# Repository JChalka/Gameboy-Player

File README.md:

# Gameboy Player
Custom Gameboy Player PCB
Currently not verified as working/functional
Use at your own risk

TODO:
Create better visuals for gamecube to GBP wiring directly to gamecube boards
Verify design
Fix signal integrity issues
Add FPGA to output a VGA/Component signal and bypass GBS-DOL chip, as well as pass through controls

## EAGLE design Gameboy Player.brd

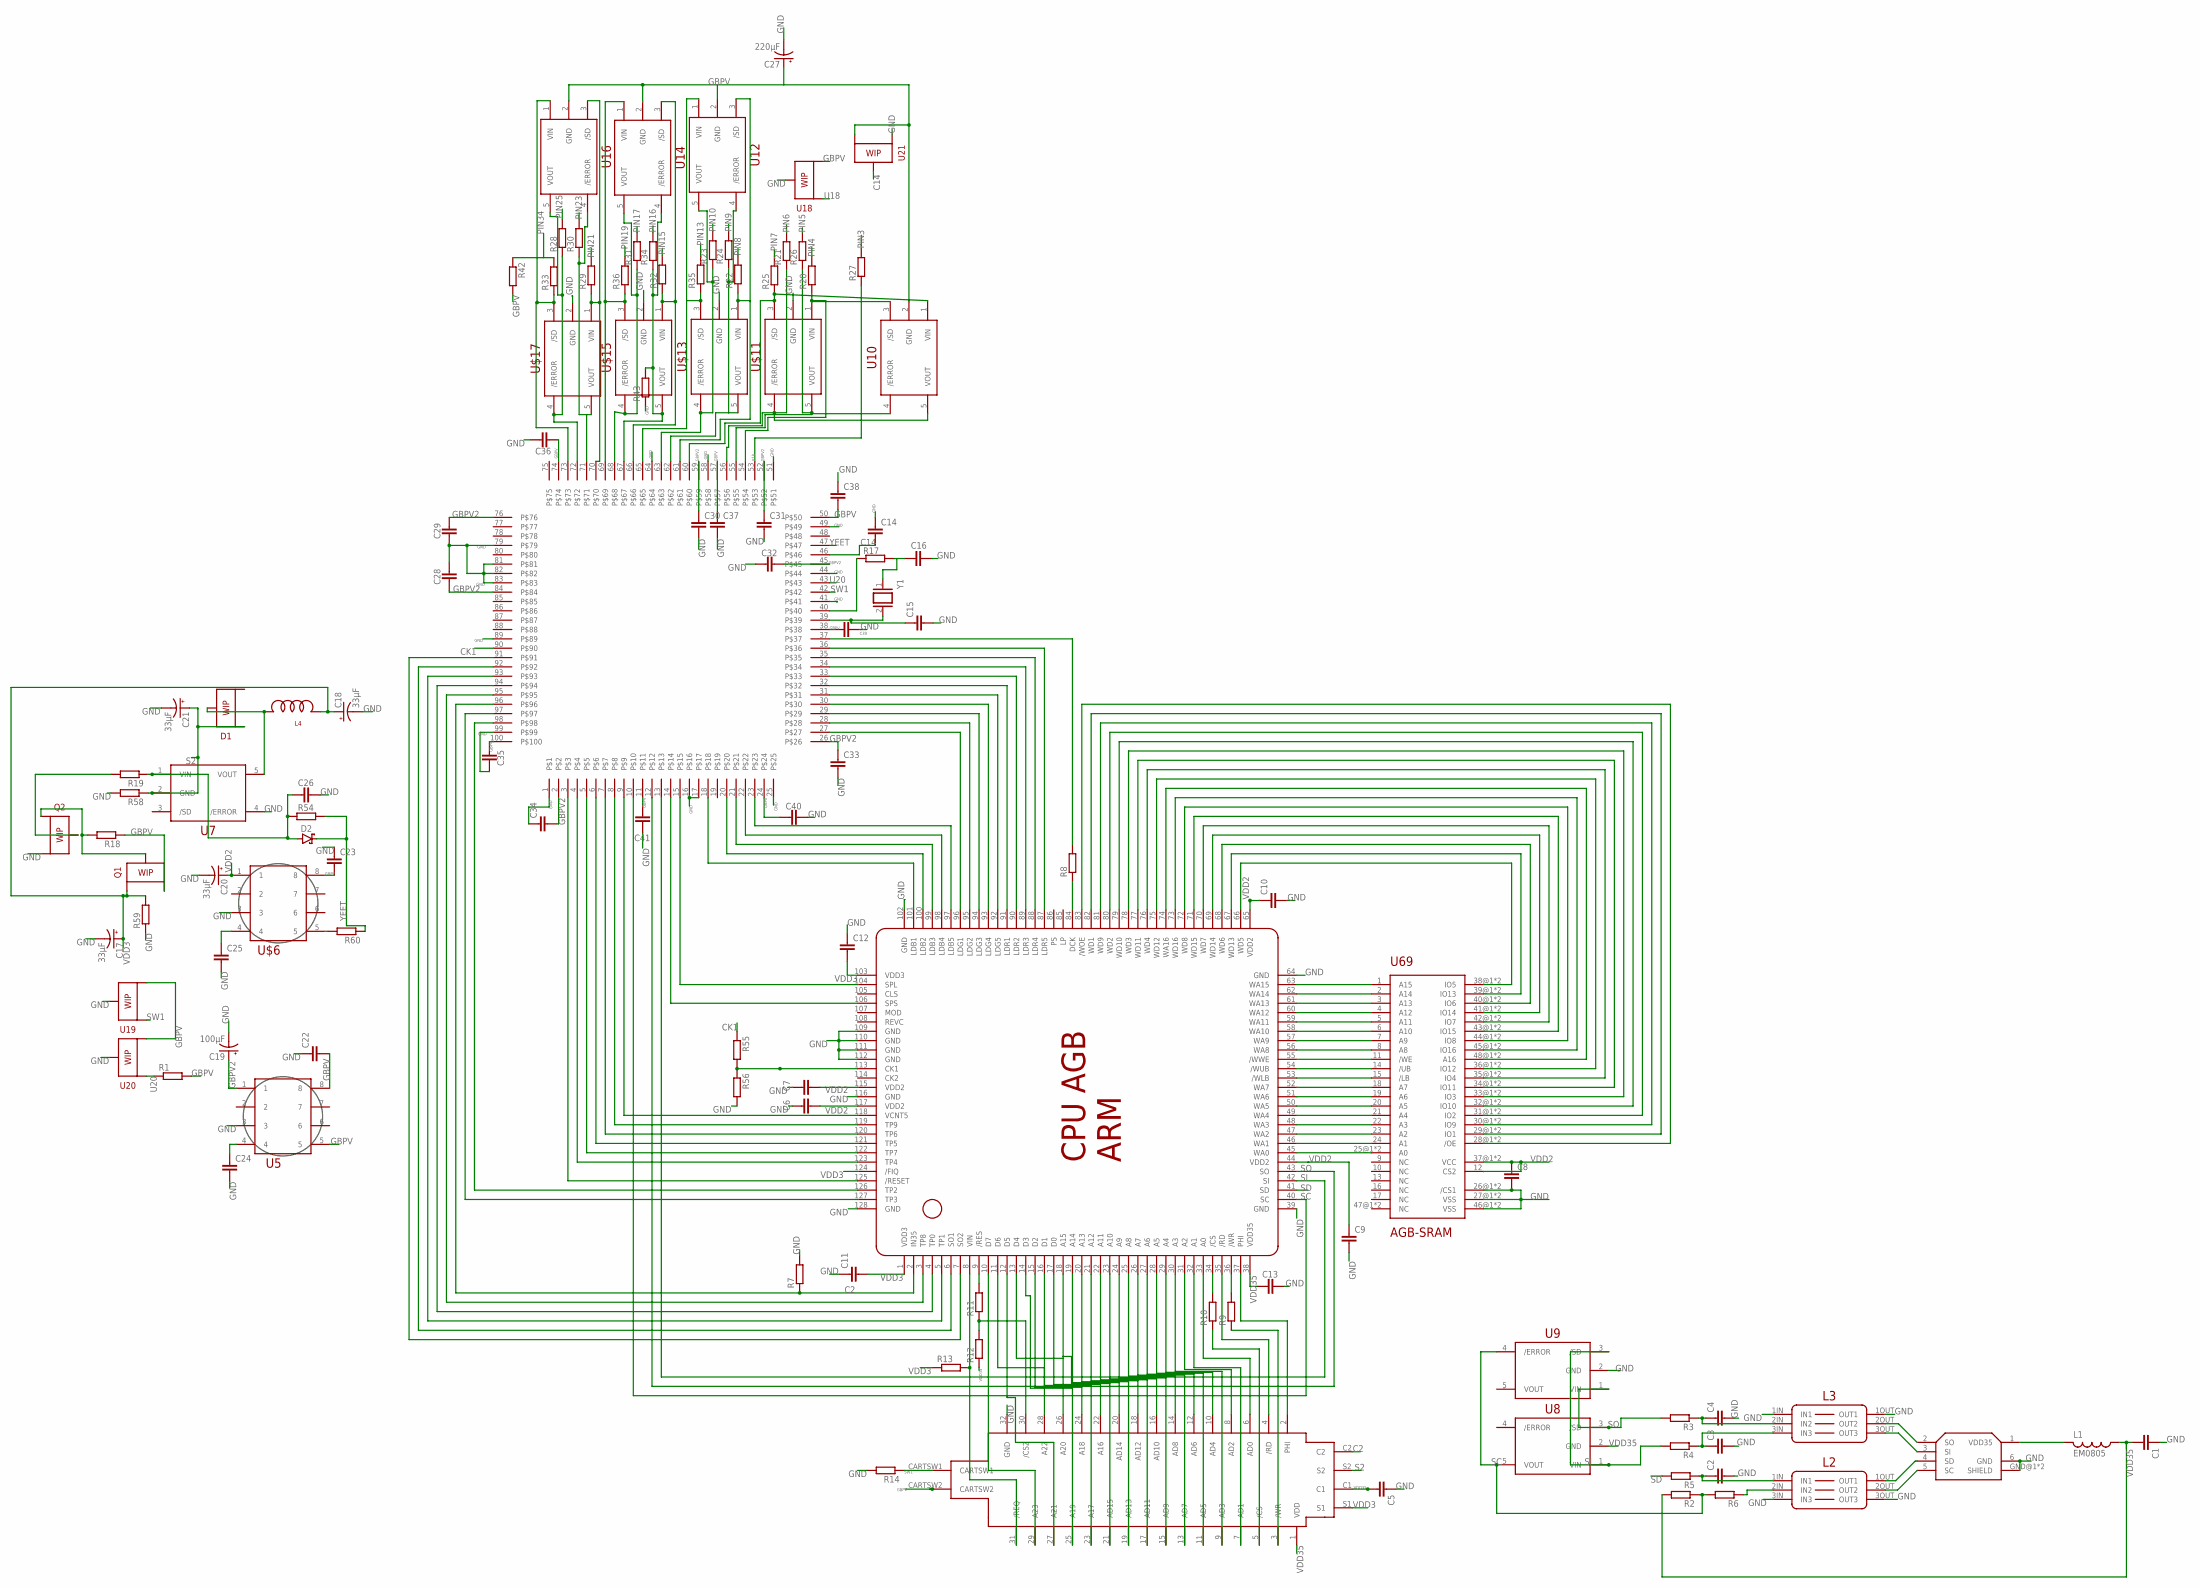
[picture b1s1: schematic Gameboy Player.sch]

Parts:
C1, C2, C3, C4, C5, C6, C7, C8, C9, C10, C11, C12, C13, C14, C15, C16, C24, C25, C28, C29, C30, C31, C32, C33, C34, C35, C36, C37, C38, C39, C40, C41: C-EUC0402; C0402
C17, C18, C20, C21: 33μF; PANASONIC_E
C19: 100μF; PANASONIC_E
C22, C23, C26: C-EUC0603; C0603
C27: 220μF; PANASONIC_E
D1: GBA-SMD-DIODE-PLACEHOLDER
D2: BAT60J; SOD323_ST
L1: EM0805; Z0805
L2, L3: GBA-TRIPLE-EMI-FILTER
L4: GBA-INDUCTOR
Q1, Q2: GBA-SMD-DIODE-PLACEHOLDER
R1, R2, R3, R4, R5, R6, R7, R8, R9, R10, R11, R12, R13, R14, R17, R18, R19, R20, R21, R22, R23, R24, R25, R26, R27, R28, R29, R30, R31, R32, R33, R34, R35, R36, R42, R43, R54, R55, R56, R58, R59, R60: RR0402; R0402
U5: GBA-TRANSFORMER
U7, U8, U9, U10, U12, U14, U16: GBA-AGB-U10
U18, U19, U20, U21: GBA-SMD-DIODE-PLACEHOLDER
U69: TSOP48-SRAM
U$1: CARTSLOT-DOL-17
U$2: CPU-AGB-LQFP128
U$3: EXT-PORT-AGB
U$4: REFQFP100; QFP50P1601X1601X120-100N
U$6: GBA-TRANSFORMER
U$11, U$13, U$15, U$17: GBA-AGB-U10
Y1: XTAL/S; QS

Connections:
C2: R7.1, U$1.C2, U$2.2 (IN35), U$4.96
C14: C14.2, U21.P$2, U$4.46
CK1: R55.1, U$4.90
GBPV: C22.2, C23.2, C27.+, C35.1, C36.2, C37.1, C38.2, C39.2, C40.1, C41.1, Q1.P$3, R1.2, R18.1, R42.2, U5.5, U5.8, U10.2 (GND), U12.2 (GND), U14.2 (GND), U16.2 (GND), U18.P$3, U19.P$3, U20.P$3, U21.P$3, U$1.CARTSW2, U$4.11, U$4.24, U$4.38, U$4.50, U$4.57, U$4.74, U$4.100, U$6.8
GBPV2: C19.+, C28.1, C29.2, C30.1, C31.1, C32.2, C33.1, C34.2, U5.1, U$4.2, U$4.26, U$4.45, U$4.52, U$4.59, U$4.76, U$4.84
GND: C1.1, C2.2, C3.2, C4.2, C5.1, C6.1, C7.1, C8.2, C9.2, C10.2, C11.1, C12.1, C13.2, C14.1, C15.2, C16.2, C17.-, C18.-, C19.-, C20.-, C21.-, C22.1, C23.1, C24.2, C25.2, C26.2, C27.-, C28.2, C29.1, C30.2, C31.2, C32.1, C33.2, C34.1, C35.2, C36.1, C37.2, C38.1, C39.1, C40.2, C41.2, L2.3IN (IN3), L2.3OUT (OUT3), L3.1IN (IN1), L3.1OUT (OUT1), Q2.P$3, R7.2, R14.2, R43.1, R56.2, R58.2, R59.1, U5.3, U7.4 (/ERROR), U9.2 (GND), U18.P$2, U19.P$2, U20.P$2, U21.P$1, U69.26@1 (/CS1), U69.26@2 (/CS1), U69.27@1 (VSS), U69.27@2 (VSS), U69.46@1 (VSS), U69.46@2 (VSS), U$1.32 (GND), U$2.39 (GND), U$2.64 (GND), U$2.102 (GND), U$2.109 (GND), U$2.110 (GND), U$2.111 (GND), U$2.112 (GND), U$2.116 (GND), U$2.128 (GND), U$3.6 (GND), U$3.GND@1 (SHIELD), U$3.GND@2 (SHIELD), U$4.1, U$4.16, U$4.17, U$4.25, U$4.41, U$4.44, U$4.49, U$4.51, U$4.58, U$4.64, U$4.79, U$4.81, U$4.82, U$4.83, U$4.89, U$4.99, U$6.3, U$11.2 (GND), U$13.2 (GND), U$15.2 (GND), U$17.2 (GND)
unnamed: U$2.87 (LDR5), U$4.36
unnamed: U$2.88 (LDR4), U$4.35
unnamed: U$2.89 (LDR3), U$4.34
unnamed: U$2.90 (LDR2), U$4.33
unnamed: U$2.91 (LDR1), U$4.32
unnamed: U$2.92 (LDG5), U$4.31
unnamed: U$2.93 (LDG4), U$4.30
unnamed: U$2.94 (LDG3), U$4.29
unnamed: U$2.95 (LDG2), U$4.28
unnamed: U$2.96 (LDG1), U$4.27
unnamed: U$2.97 (LDB5), U$4.23
unnamed: U$2.98 (LDB4), U$4.22
unnamed: U$2.99 (LDB3), U$4.21
unnamed: U$2.100 (LDB2), U$4.20
unnamed: U$2.101 (LDB1), U$4.18
unnamed: U$2.104 (SPL), U$4.15
unnamed: U$2.106 (SPS), U$4.14
unnamed: C15.1, U$4.39, Y1.2
unnamed: U$2.3 (TP8), U$4.95
unnamed: U$2.4 (TP0), U$4.94
unnamed: U$2.5 (TP1), U$4.93
unnamed: U$2.6 (SO1), U$4.92
unnamed: U$2.7 (SO2), U$4.91
unnamed: U$2.127 (TP3), U$4.97
unnamed: U$2.126 (TP2), U$4.98
unnamed: U$2.125 (/RESET), U$4.3
unnamed: U$2.123 (TP4), U$4.4
unnamed: U$2.122 (TP7), U$4.5
unnamed: U$2.121 (TP5), U$4.6
unnamed: U$2.120 (TP6), U$4.7
unnamed: U$2.119 (TP9), U$4.8
unnamed: U$2.118 (VCNT5), U$4.9
unnamed: R8.1, U$2.84 (DCK)
unnamed: R8.2, U$4.37
unnamed: U69.25@1 (A0), U69.25@2 (A0), U$2.45 (WA0)
unnamed: U69.24 (A1), U$2.46 (WA1)
unnamed: U69.23 (A2), U$2.47 (WA2)
unnamed: U69.22 (A3), U$2.48 (WA3)
unnamed: U69.21 (A4), U$2.49 (WA4)
unnamed: U69.20 (A5), U$2.50 (WA5)
unnamed: U69.19 (A6), U$2.51 (WA6)
unnamed: U69.18 (A7), U$2.52 (WA7)
unnamed: U69.15 (/LB), U$2.53 (/WLB)
unnamed: U69.14 (/UB), U$2.54 (/WUB)
unnamed: U69.11 (/WE), U$2.55 (/WWE)
unnamed: U69.8 (A8), U$2.56 (WA8)
unnamed: U69.7 (A9), U$2.57 (WA9)
unnamed: U69.6 (A10), U$2.58 (WA10)
unnamed: U69.5 (A11), U$2.59 (WA11)
unnamed: U69.4 (A12), U$2.60 (WA12)
unnamed: U69.3 (A13), U$2.61 (WA13)
unnamed: U69.2 (A14), U$2.62 (WA14)
unnamed: U69.1 (A15), U$2.63 (WA15)
unnamed: U69.38@1 (IO5), U69.38@2 (IO5), U$2.66 (WD5)
unnamed: U69.39@1 (IO13), U69.39@2 (IO13), U$2.67 (WD13)
unnamed: U69.40@1 (IO6), U69.40@2 (IO6), U$2.68 (WD6)
unnamed: U69.41@1 (IO14), U69.41@2 (IO14), U$2.69 (WD14)
unnamed: U69.42@1 (IO7), U69.42@2 (IO7), U$2.70 (WD7)
unnamed: U69.43@1 (IO15), U69.43@2 (IO15), U$2.71 (WD15)
unnamed: U69.44@1 (IO8), U69.44@2 (IO8), U$2.72 (WD8)
unnamed: U69.45@1 (IO16), U69.45@2 (IO16), U$2.73 (WD16)
unnamed: U69.48@1 (A16), U69.48@2 (A16), U$2.74 (WA16)
unnamed: U69.36@1 (IO12), U69.36@2 (IO12), U$2.75 (WD12)
unnamed: U69.35@1 (IO4), U69.35@2 (IO4), U$2.76 (WD4)
unnamed: U69.34@1 (IO11), U69.34@2 (IO11), U$2.77 (WD11)
unnamed: U69.33@1 (IO3), U69.33@2 (IO3), U$2.78 (WD3)
unnamed: U69.32@1 (IO10), U69.32@2 (IO10), U$2.79 (WD10)
unnamed: U69.31@1 (IO2), U69.31@2 (IO2), U$2.80 (WD2)
unnamed: U69.30@1 (IO9), U69.30@2 (IO9), U$2.81 (WD9)
unnamed: U69.29@1 (IO1), U69.29@2 (IO1), U$2.82 (WD1)
unnamed: U69.28@1 (/OE), U69.28@2 (/OE), U$2.83 (/WOE)
unnamed: U$1.6 (AD0), U$2.33 (A0)
unnamed: R10.1, U$1.5 (/CS)
unnamed: U$1.4 (/RD), U$2.35 (/RD)
unnamed: R9.1, U$1.3 (/WR)
unnamed: R10.2, U$2.34 (/CS)
unnamed: R9.2, U$2.36 (/WR)
unnamed: U$1.2 (PHI), U$2.37 (PHI)
unnamed: R13.2, U$1.31 (/REQ), U$2.8 (VIN)
unnamed: R11.1, R12.2, U$1.30 (/CS2)
unnamed: R11.2, U$2.9 (/RES)
unnamed: U$1.29 (A23), U$2.10 (D7)
unnamed: U$1.28 (A22), U$2.11 (D6)
unnamed: R33.1, U16.1 (VIN), U$4.73, U$17.3 (/SD)
unnamed: U$1.26 (A20), U$2.13 (D4)
unnamed: U$1.7 (AD1), U$2.32 (A1)
unnamed: U$1.8 (AD2), U$2.31 (A2)
unnamed: U$1.9 (AD3), U$2.30 (A3)
unnamed: U$1.10 (AD4), U$2.29 (A4)
unnamed: U$1.11 (AD5), U$2.28 (A5)
unnamed: U$1.12 (AD6), U$2.27 (A6)
unnamed: U$1.13 (AD7), U$2.26 (A7)
unnamed: U$1.14 (AD8), U$2.25 (A8)
unnamed: U$1.15 (AD9), U$2.24 (A9)
unnamed: U$1.16 (AD10), U$2.23 (A10)
unnamed: U$1.17 (AD11), U$2.22 (A11)
unnamed: U$1.18 (AD12), U$2.21 (A12)
unnamed: U$1.19 (AD13), U$2.20 (A13)
unnamed: U$1.20 (AD14), U$2.19 (A14)
unnamed: U$1.21 (AD15), U$2.18 (A15)
unnamed: U$1.22 (A16), U$2.17 (D0)
unnamed: U$1.23 (A17), U$2.16 (D1)
unnamed: U$1.24 (A18), U$2.15 (D2)
unnamed: U$1.25 (A19), U$2.14 (D3)
unnamed: U$1.27 (A21), U$2.12 (D5)
unnamed: R28.1, U16.5 (VOUT), U$4.72, U$17.4 (/ERROR)
unnamed: R30.1, U16.4 (/ERROR), U$4.71, U$17.5 (VOUT)
unnamed: R29.1, U16.3 (/SD), U$4.70, U$17.1 (VIN)
unnamed: R36.1, U14.1 (VIN), U$4.69, U$15.3 (/SD)
unnamed: R31.1, U14.5 (VOUT), U$4.68, U$15.4 (/ERROR)
unnamed: R34.1, R43.2, U14.4 (/ERROR), U$4.67, U$15.5 (VOUT)
unnamed: R32.1, U14.3 (/SD), U$4.66, U$15.1 (VIN)
unnamed: R35.1, U12.1 (VIN), U$4.65, U$13.3 (/SD)
unnamed: R23.1, U12.5 (VOUT), U$4.63, U$13.4 (/ERROR)
unnamed: R24.1, U12.4 (/ERROR), U$4.62, U$13.5 (VOUT)
unnamed: R22.1, U12.3 (/SD), U$4.61, U$13.1 (VIN)
unnamed: R25.1, U10.1 (VIN), U$4.60, U$11.3 (/SD)
unnamed: R21.1, U10.5 (VOUT), U$4.56, U$11.4 (/ERROR)
unnamed: R26.1, U10.4 (/ERROR), U$4.55, U$11.5 (VOUT)
unnamed: R20.1, U10.3 (/SD), U$4.54, U$11.1 (VIN)
unnamed: R17.1, U$4.40
unnamed: C16.1, R17.2, Y1.1
unnamed: R60.2, U$6.5
unnamed: L1.2, U$3.1 (VDD35)
unnamed: C2.1, L2.1IN (IN1), R5.1
unnamed: C3.1, L3.3IN (IN3), R4.1
unnamed: L2.2IN (IN2), R6.1
unnamed: R55.2, R56.1, U$2.113 (CK1)
unnamed: C26.1, D2.A, R19.1, R54.1, U7.1 (VIN)
unnamed: C25.1, U$6.4
unnamed: Q2.P$2, R19.2
unnamed: Q1.P$2, Q2.P$1, R18.2
unnamed: C24.1, U5.4
unnamed: D1.P$2, L4.2@1 (2), L4.2@2 (2), U7.5 (VOUT)
unnamed: L2.1OUT (OUT1), U$3.4 (SD)
unnamed: L2.2OUT (OUT2), U$3.5 (SC)
unnamed: L3.3OUT (OUT3), U$3.3 (SI)
unnamed: L3.2OUT (OUT2), U$3.2 (SO)
unnamed: C4.1, L3.2IN (IN2), R3.1
PIN3: R27.2
PIN4: R20.2
PIN5: R26.2
PIN6: R21.2
PIN7: R25.2
PIN8: R22.2
PIN9: R24.2
PIN10: R23.2
PIN13: R35.2
PIN15: R32.2
PIN16: R34.2
PIN17: R31.2
PIN19: R36.2
PIN21: R29.2
PIN23: R30.2
PIN25: R28.2
PIN34: R33.2, R42.1
S2: C21.+, D1.P$1, R58.1, U7.2 (GND), U$1.S2
SC: R2.1, R6.2, U8.5 (VOUT), U9.4 (/ERROR), U$2.40 (SC), U$4.10
SD: R5.2, U$2.41 (SD)
SI: R4.2, U8.1 (VIN), U9.3 (/SD), U$2.42 (SI), U$4.13
SO: R3.2, U8.3 (/SD), U9.1 (VIN), U$2.43 (SO), U$4.12
SW1: R14.1, U19.P$1, U$1.CARTSW1, U$4.42
U18: R27.1, U18.P$1, U$4.53
U20: R1.1, U20.P$1, U$4.43
VDD2: C6.2, C7.2, C8.1, C9.1, C10.1, C20.+, U69.12 (CS2), U69.37@1 (VCC), U69.37@2 (VCC), U$2.44 (VDD2), U$2.65 (VDD2), U$2.115 (VDD2), U$2.117 (VDD2), U$6.1
VDD3: C11.2, C12.2, C17.+, C18.+, L4.1@1 (1), L4.1@2 (1), Q1.P$1, R13.1, R59.2, U$1.S1, U$2.1 (VDD3), U$2.103 (VDD3), U$2.124 (/FIQ)
VDD35: C1.2, C5.2, C13.1, L1.1, R2.2, R12.1, U8.2 (GND), U$1.1 (VDD), U$1.C1, U$2.38 (VDD35)
YEET: D2.C, R54.2, R60.1, U$4.47

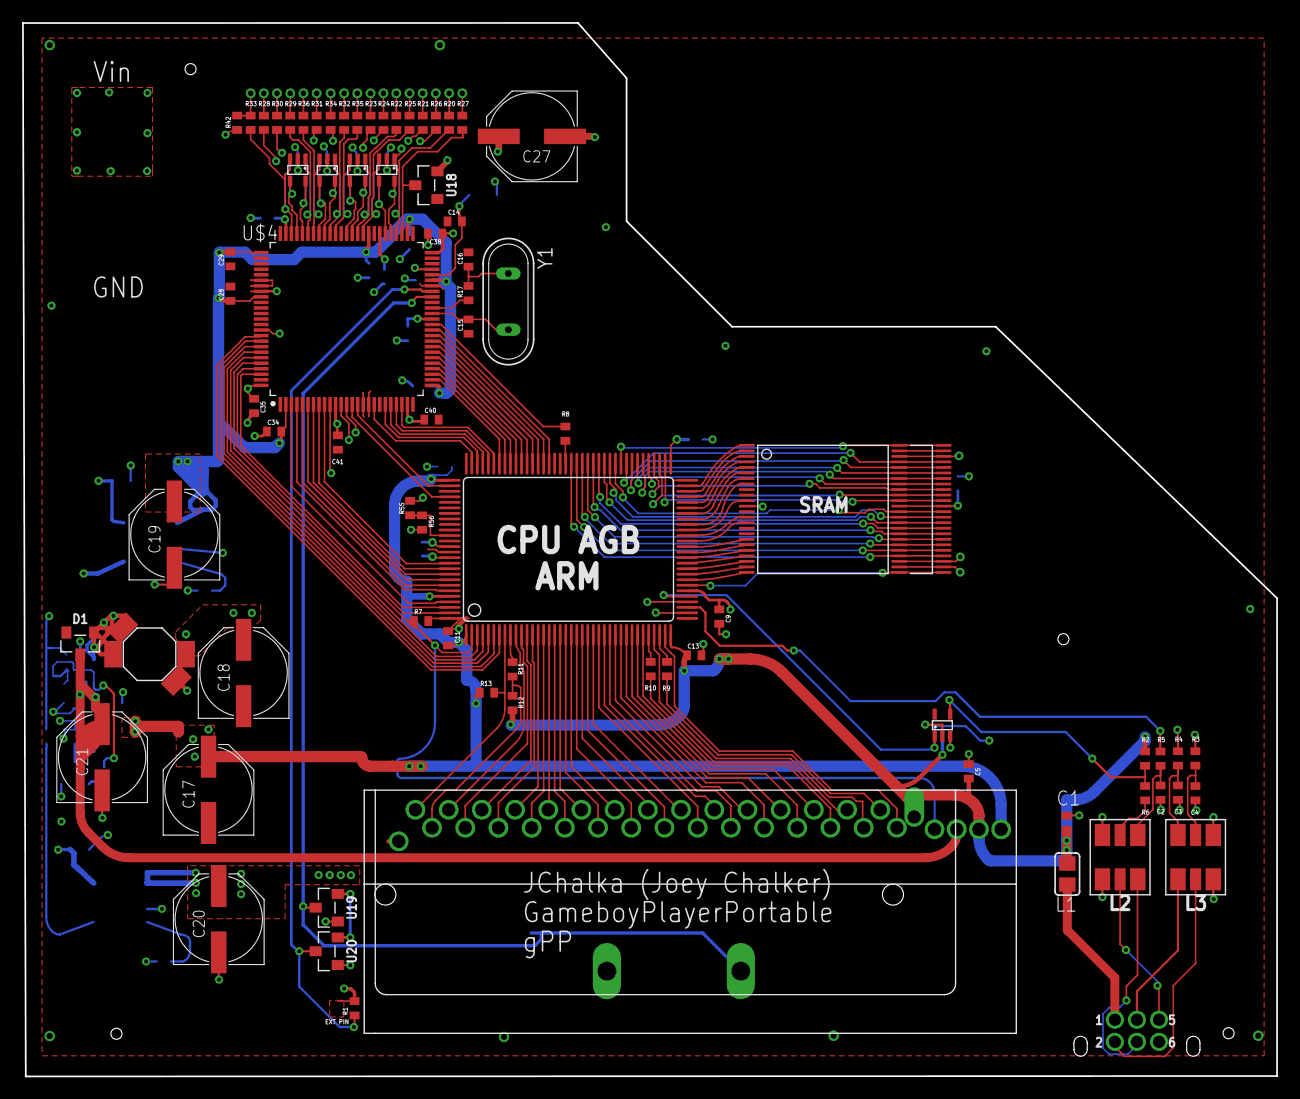
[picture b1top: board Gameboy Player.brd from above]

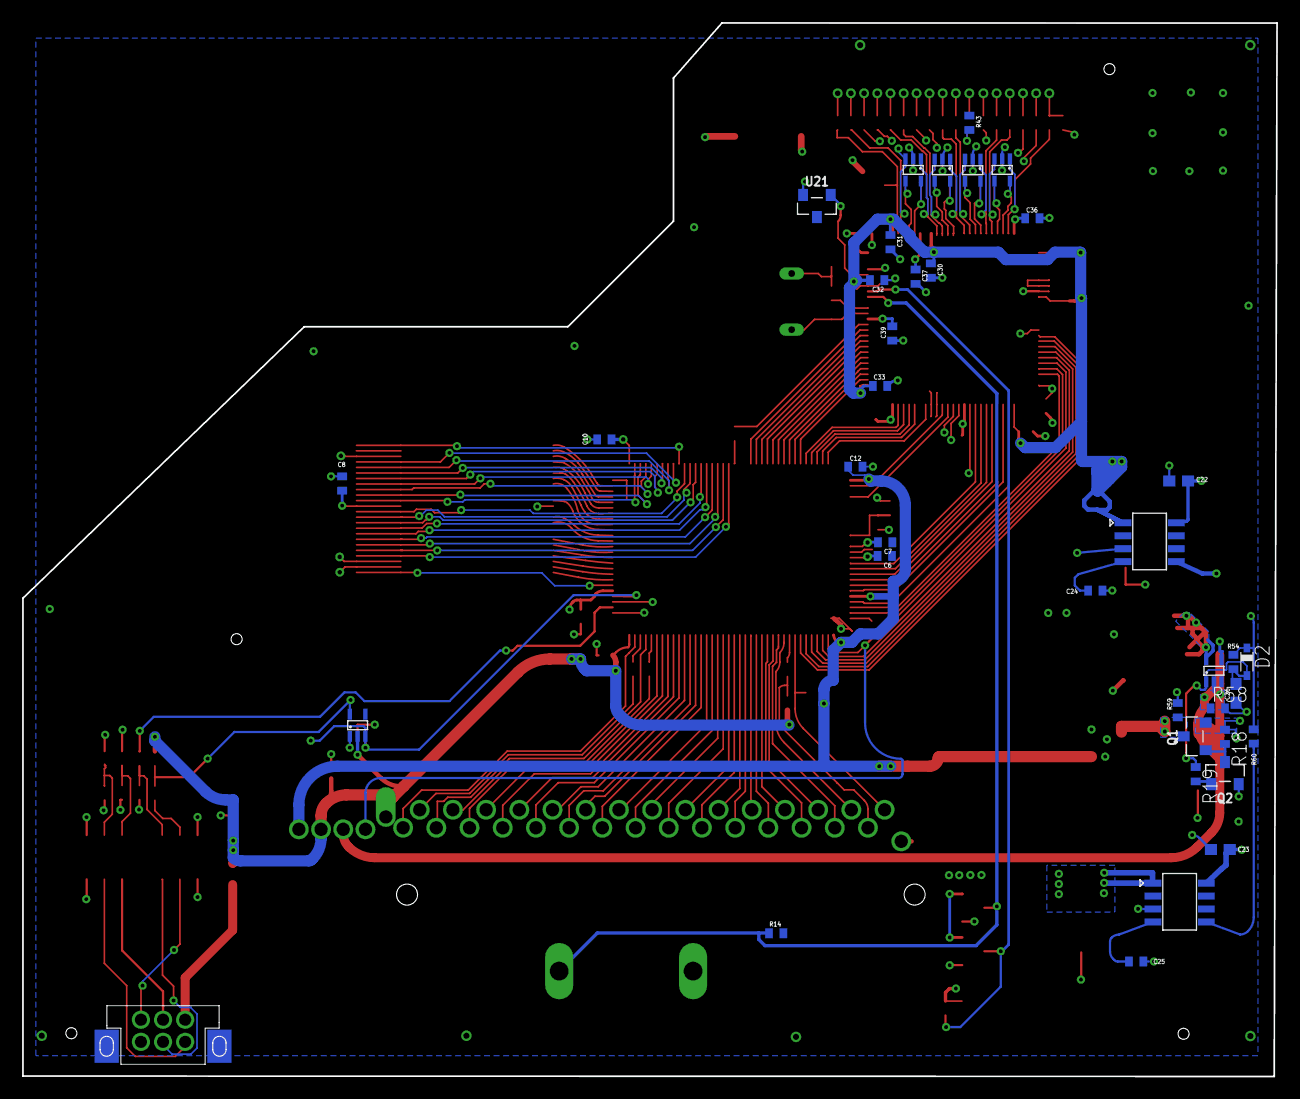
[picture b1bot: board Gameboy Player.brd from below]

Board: 4 copper layers, 113.5 x 95.3 mm, 114 parts (38 on the bottom side), 158 nets.

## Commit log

2022-03-13 Initial Commit
    Add Gameboy Player.brd
    Add Gameboy Player.sch
    Add Library Files
    Add Gerber Files (DO NOT ORDER)
    Project currently tested as not-working, use at your own risk
2022-03-13 add PCB Scans
2022-03-13 Update Libraries
2022-03-13 update images
